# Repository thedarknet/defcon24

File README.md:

# defcon24

Badge Directory has the badge firmware, the eagle files and documentation for components used on the badge.

BadgeGen is a tool used to generate key pairs, and unique radio ids.  This tool can also solve some of the crypto's this was done simply to save typing on the badge itself.

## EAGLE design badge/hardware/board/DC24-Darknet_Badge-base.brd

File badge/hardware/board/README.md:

# Badge hardware

	DC24-Darknet_Badge.*		The starting circuit which has both the base and the shield included
	DC24-Darknet_Badge-base.*	The final base board with puzzles in the silk screen
	DC24-Darknet_Badge-shield.*	The final shield board with puzzles in the silk screen

Note to get the boards made at OSH Park, you need to submit the individual boards base and shield. 
The combined file is strictly for the full schematic.

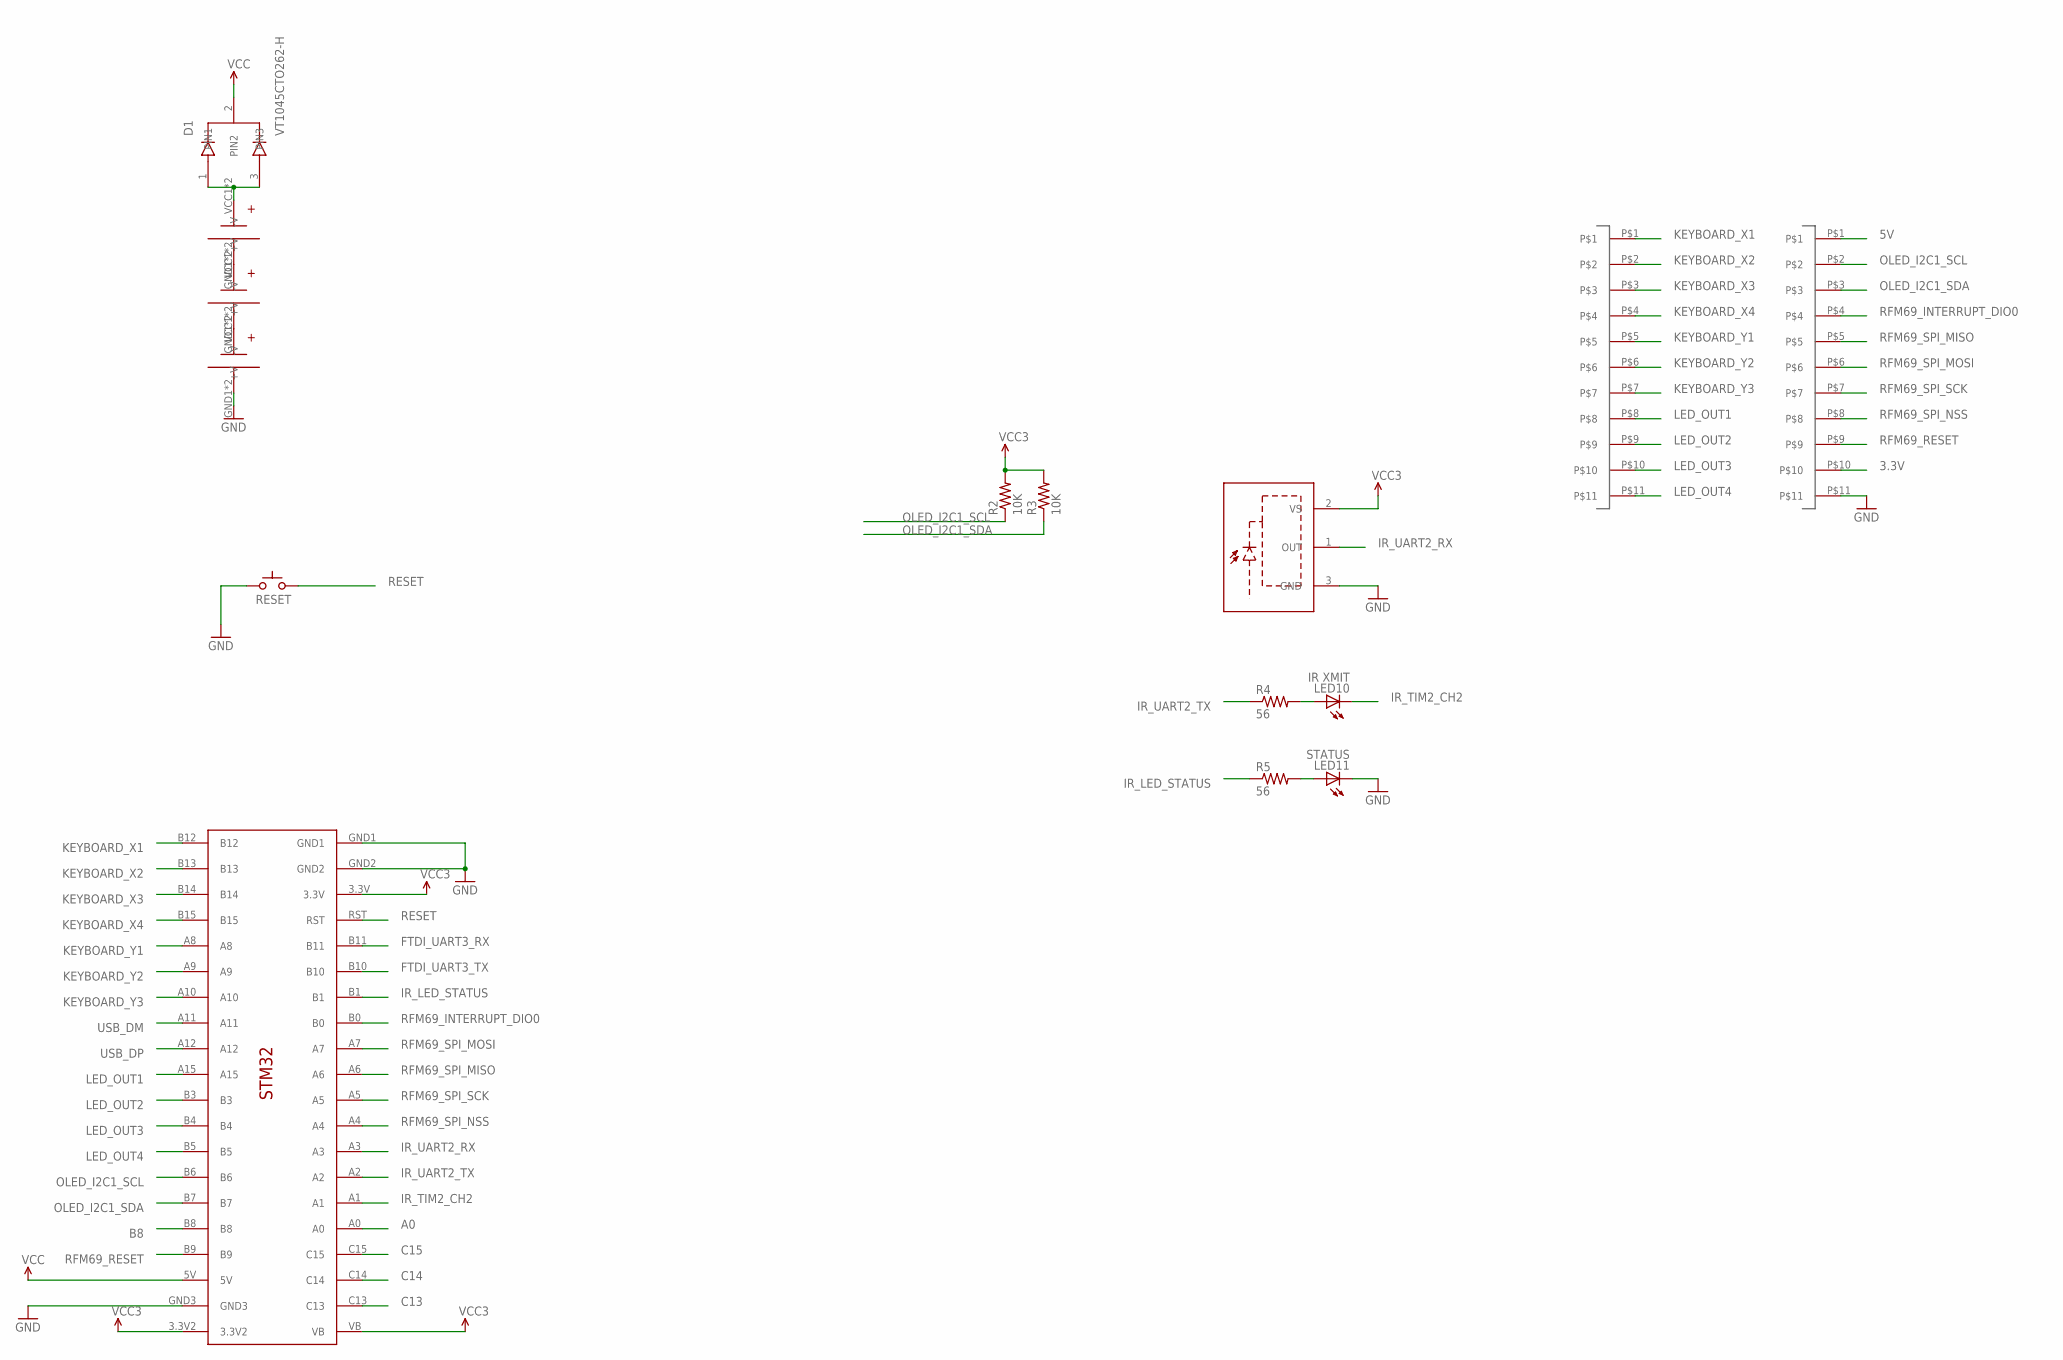
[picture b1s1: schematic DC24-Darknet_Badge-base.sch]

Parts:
D1: VT1045CTO262-H; TO262-H
LED10: IR XMIT; LED5MM-EDGE
LED11: STATUS; LED5MM-EDGE
R2, R3: 10K; AXIAL-0.3
R4, R5: 56; AXIAL-0.3
RESET: SWITCH_TACTILETACTILE-2PIN-NARROW; TACTILE-2PIN-NARROW
U1: SOP22; IR-MODULE
U$3, U$4, U$5: AAA_BATTERYAAA_BATTERY_CLIP; AAA_BATTERY_CLIP
U$14, U$17: HEADER_11PIN; 1X11
U$15: STM32_DEV_BOARDSTM32_DEV_BOARD; STM32_DEV_BOARD

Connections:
3.3V: R2.P$2 (2), R3.P$2 (2), U1.2 (VS), U$15.3.3V, U$15.3.3V2, U$15.VB, U$17.P$10
5V: D1.2 (PIN2), U$15.5V, U$17.P$1
A0: U$15.A0
B8: U$15.B8
C13: U$15.C13
C14: U$15.C14
C15: U$15.C15
FTDI_UART3_RX: U$15.B11
FTDI_UART3_TX: U$15.B10
GND: LED11.K (C), RESET.P$2 (C), U1.3 (GND), U$5.GND1 (-V), U$5.GND2 (-V), U$15.GND1, U$15.GND2, U$15.GND3, U$17.P$11
IR_LED_STATUS: R5.P$1 (1), U$15.B1
IR_TIM2_CH2: LED10.K (C), U$15.A1
IR_UART2_RX: U1.1 (OUT), U$15.A3
IR_UART2_TX: R4.P$1 (1), U$15.A2
KEYBOARD_X1: U$14.P$1, U$15.B12
KEYBOARD_X2: U$14.P$2, U$15.B13
KEYBOARD_X3: U$14.P$3, U$15.B14
KEYBOARD_X4: U$14.P$4, U$15.B15
KEYBOARD_Y1: U$14.P$5, U$15.A8
KEYBOARD_Y2: U$14.P$6, U$15.A9
KEYBOARD_Y3: U$14.P$7, U$15.A10
LED_OUT1: U$14.P$8, U$15.A15
LED_OUT2: U$14.P$9, U$15.B3
LED_OUT3: U$14.P$10, U$15.B4
LED_OUT4: U$14.P$11, U$15.B5
unnamed: LED10.A, R4.P$2 (2)
unnamed: LED11.A, R5.P$2 (2)
unnamed: D1.1 (PIN1), D1.3 (PIN3), U$3.VCC1 (+V), U$3.VCC2 (+V)
unnamed: U$3.GND1 (-V), U$3.GND2 (-V), U$4.VCC1 (+V), U$4.VCC2 (+V)
unnamed: U$4.GND1 (-V), U$4.GND2 (-V), U$5.VCC1 (+V), U$5.VCC2 (+V)
OLED_I2C1_SCL: R2.P$1 (1), U$15.B6, U$17.P$2
OLED_I2C1_SDA: R3.P$1 (1), U$15.B7, U$17.P$3
RESET: RESET.P$1 (A), U$15.RST
RFM69_INTERRUPT_DIO0: U$15.B0, U$17.P$4
RFM69_RESET: U$15.B9, U$17.P$9
RFM69_SPI_MISO: U$15.A6, U$17.P$5
RFM69_SPI_MOSI: U$15.A7, U$17.P$6
RFM69_SPI_NSS: U$15.A4, U$17.P$8
RFM69_SPI_SCK: U$15.A5, U$17.P$7
USB_DM: U$15.A11
USB_DP: U$15.A12

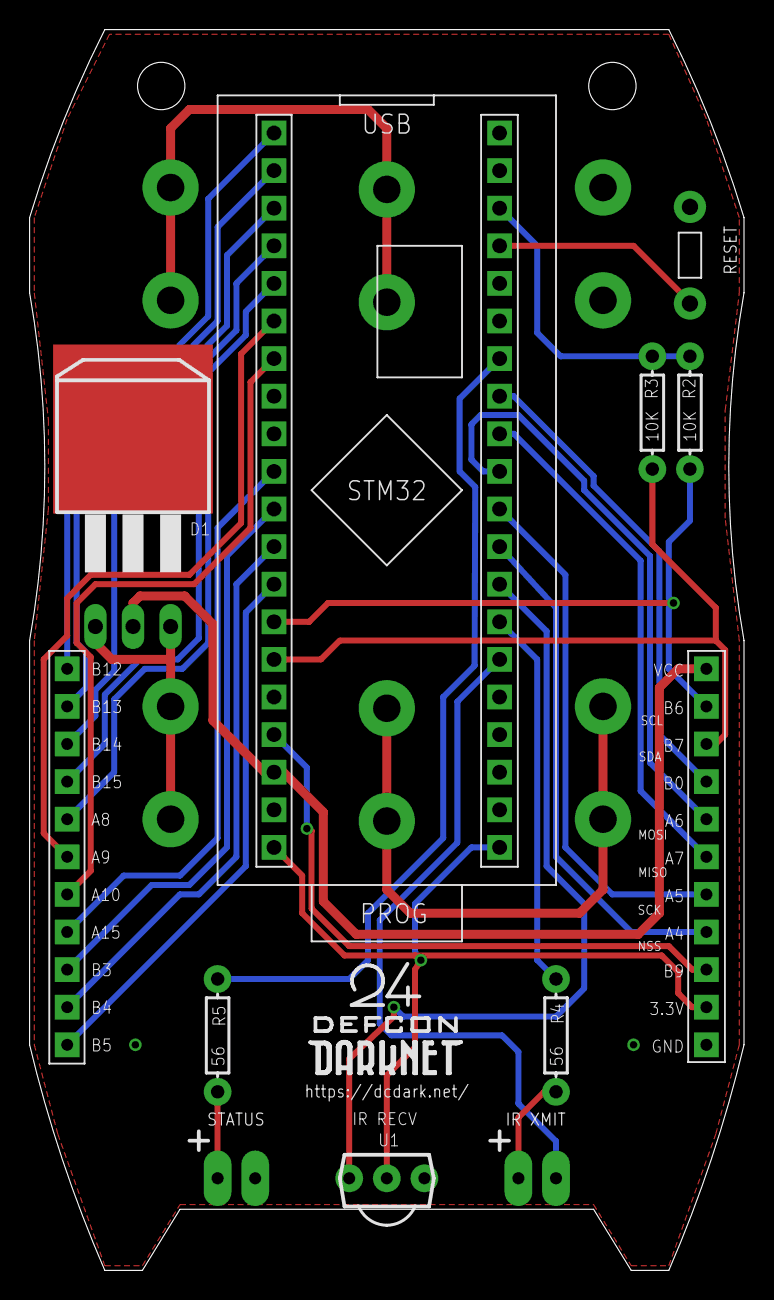
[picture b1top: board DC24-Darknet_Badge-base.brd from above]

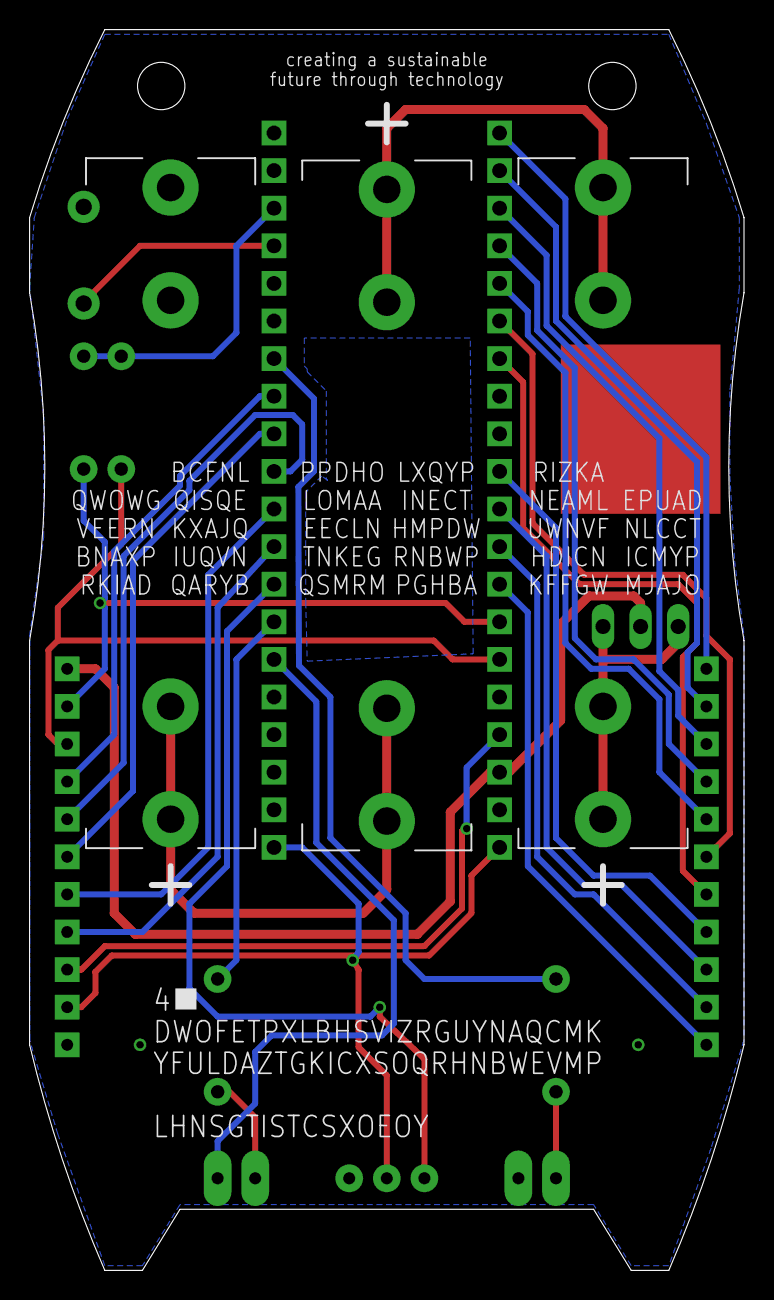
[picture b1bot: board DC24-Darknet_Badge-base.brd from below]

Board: 2 copper layers, 48.3 x 83.8 mm, 15 parts (3 on the bottom side), 32 nets.

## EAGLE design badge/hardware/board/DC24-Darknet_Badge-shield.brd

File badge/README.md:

Install Dev Env:
* go here:  http://gnuarmeclipse.github.io/ for background and step by step

Basic steps:

* Install eclipse Luna CDT (c++ env)

* add a new market place:  

name: GNU ARM Eclipse Plug-ins
URL: http://gnuarmeclipse.sourceforge.net/updates

You will see the ecplise arm plugin select it and it will install for you.

If you get complaints about missing software I found these links helpful.

* apt-get install gcc-arm-none-eabi (or something close to that)

* apt-get install openocd Or download from to configure openocd in eclipse look here: http://gnuarmeclipse.github.io/debug/openocd/ OR to download new version of openocd:  http://gnuarmeclipse.github.io/openocd/download/

Then close this repo and then import this directory into you're workspace (remeber to uncheck the option to copy all files to your workspace).

Debug configuration:

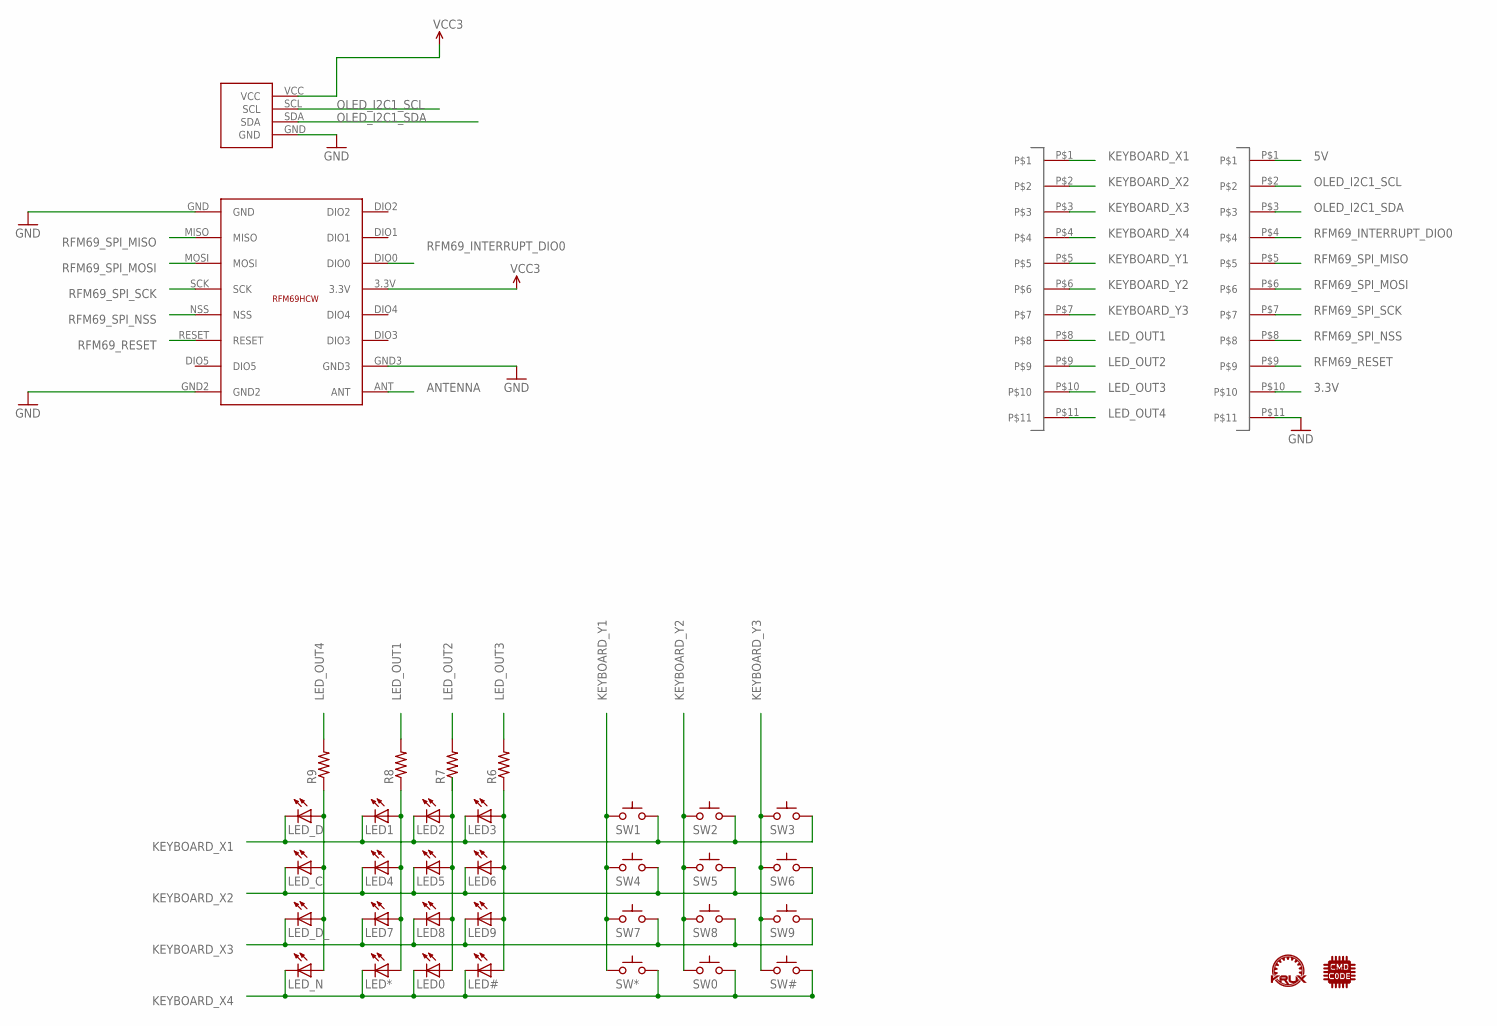
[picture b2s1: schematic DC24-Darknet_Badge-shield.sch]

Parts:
LED0, LED1, LED2, LED3, LED4, LED5, LED6, LED7, LED8, LED9: LEDREVERSEMOUNT; GULLWING_LED
LED#: LEDREVERSEMOUNT; GULLWING_LED
LED*: LEDREVERSEMOUNT; GULLWING_LED
LED_C: LEDREVERSEMOUNT; GULLWING_LED
LED_D: LEDREVERSEMOUNT; GULLWING_LED
LED_D_: LEDREVERSEMOUNT; GULLWING_LED
LED_N: LEDREVERSEMOUNT; GULLWING_LED
R6, R7, R8, R9: RESISTOR1206; 1206
SW0, SW1, SW2, SW3, SW4, SW5, SW6, SW7, SW8, SW9: SWITCH_TACTILETACTILE-2PIN-NARROW; TACTILE-2PIN-NARROW
SW#: SWITCH_TACTILETACTILE-2PIN-NARROW; TACTILE-2PIN-NARROW
SW*: SWITCH_TACTILETACTILE-2PIN-NARROW; TACTILE-2PIN-NARROW
U$1: I2C_0.96_OLEDOLED; I2C_0.96_OLED
U$2: RFM69HCWRFN69HCWSMD; 16PIN-PCB-SMD
U$6, U$13: HEADER_11PIN; 1X11
U$21: KRUX_LOGO
U$23: CMD_C0DE_LOGO

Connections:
3.3V: U$1.VCC, U$2.3.3V, U$13.P$10
5V: U$13.P$1
ANTENNA: U$2.ANT
GND: U$1.GND, U$2.GND, U$2.GND2, U$2.GND3, U$13.P$11
KEYBOARD_X1: LED1.C, LED2.C, LED3.C, LED_D.C, SW1.P$1 (A), SW2.P$1 (A), SW3.P$1 (A), U$6.P$1
KEYBOARD_X2: LED4.C, LED5.C, LED6.C, LED_C.C, SW4.P$1 (A), SW5.P$1 (A), SW6.P$1 (A), U$6.P$2
KEYBOARD_X3: LED7.C, LED8.C, LED9.C, LED_D_.C, SW7.P$1 (A), SW8.P$1 (A), SW9.P$1 (A), U$6.P$3
KEYBOARD_X4: LED0.C, LED#.C, LED*.C, LED_N.C, SW0.P$1 (A), SW#.P$1 (A), SW*.P$1 (A), U$6.P$4
KEYBOARD_Y1: SW1.P$2 (C), SW4.P$2 (C), SW7.P$2 (C), SW*.P$2 (C), U$6.P$5
KEYBOARD_Y2: SW0.P$2 (C), SW2.P$2 (C), SW5.P$2 (C), SW8.P$2 (C), U$6.P$6
KEYBOARD_Y3: SW3.P$2 (C), SW6.P$2 (C), SW9.P$2 (C), SW#.P$2 (C), U$6.P$7
LED_OUT1: R8.2, U$6.P$8
LED_OUT2: R7.2, U$6.P$9
LED_OUT3: R6.2, U$6.P$10
LED_OUT4: R9.2, U$6.P$11
unnamed: LED3.A, LED6.A, LED9.A, LED#.A, R6.1
unnamed: LED0.A, LED2.A, LED5.A, LED8.A, R7.1
unnamed: LED1.A, LED4.A, LED7.A, LED*.A, R8.1
unnamed: LED_C.A, LED_D.A, LED_D_.A, LED_N.A, R9.1
OLED_I2C1_SCL: U$1.SCL, U$13.P$2
OLED_I2C1_SDA: U$1.SDA, U$13.P$3
RFM69_INTERRUPT_DIO0: U$2.DIO0, U$13.P$4
RFM69_RESET: U$2.RESET, U$13.P$9
RFM69_SPI_MISO: U$2.MISO, U$13.P$5
RFM69_SPI_MOSI: U$2.MOSI, U$13.P$6
RFM69_SPI_NSS: U$2.NSS, U$13.P$8
RFM69_SPI_SCK: U$2.SCK, U$13.P$7

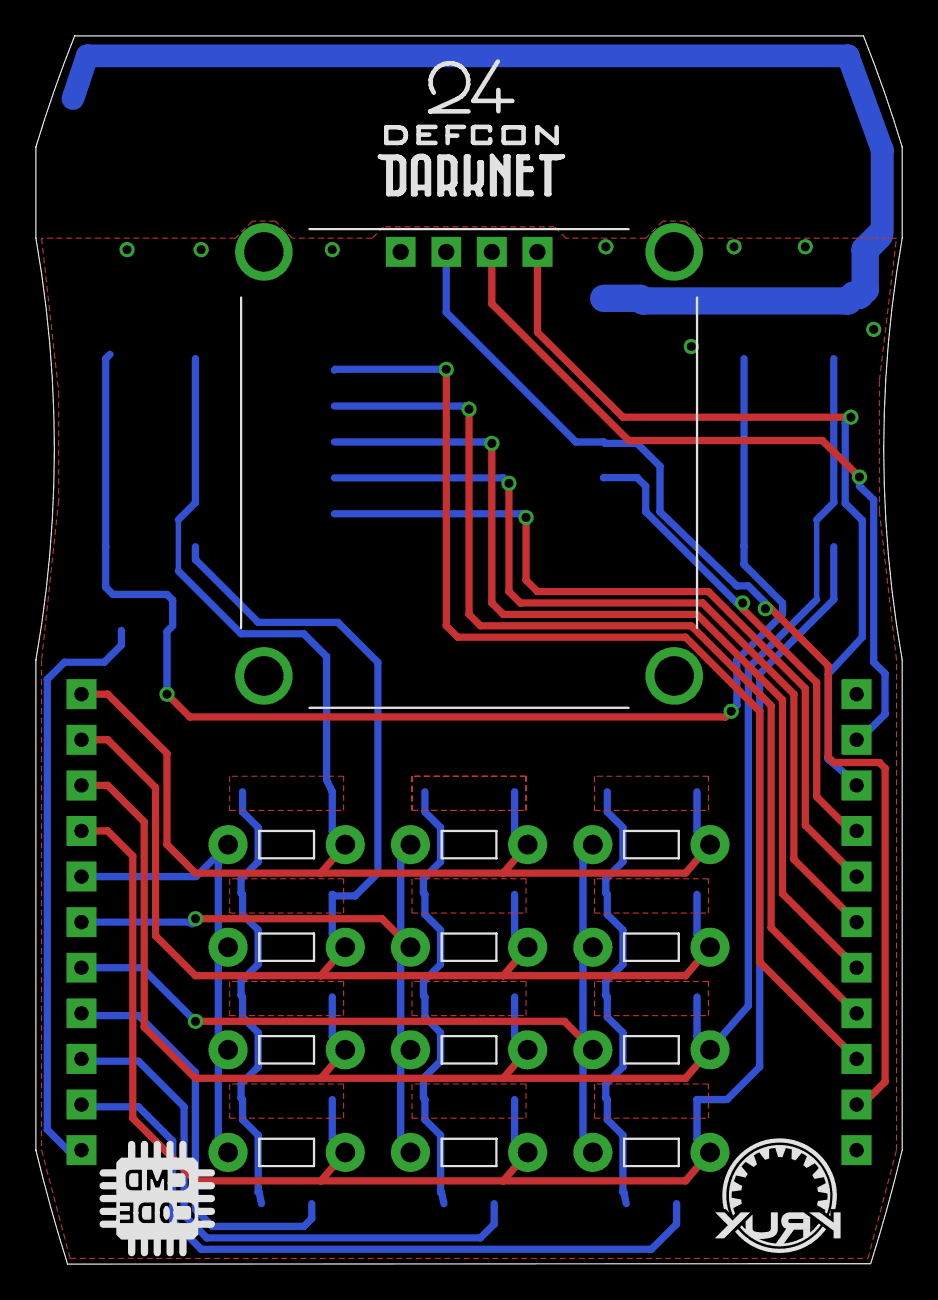
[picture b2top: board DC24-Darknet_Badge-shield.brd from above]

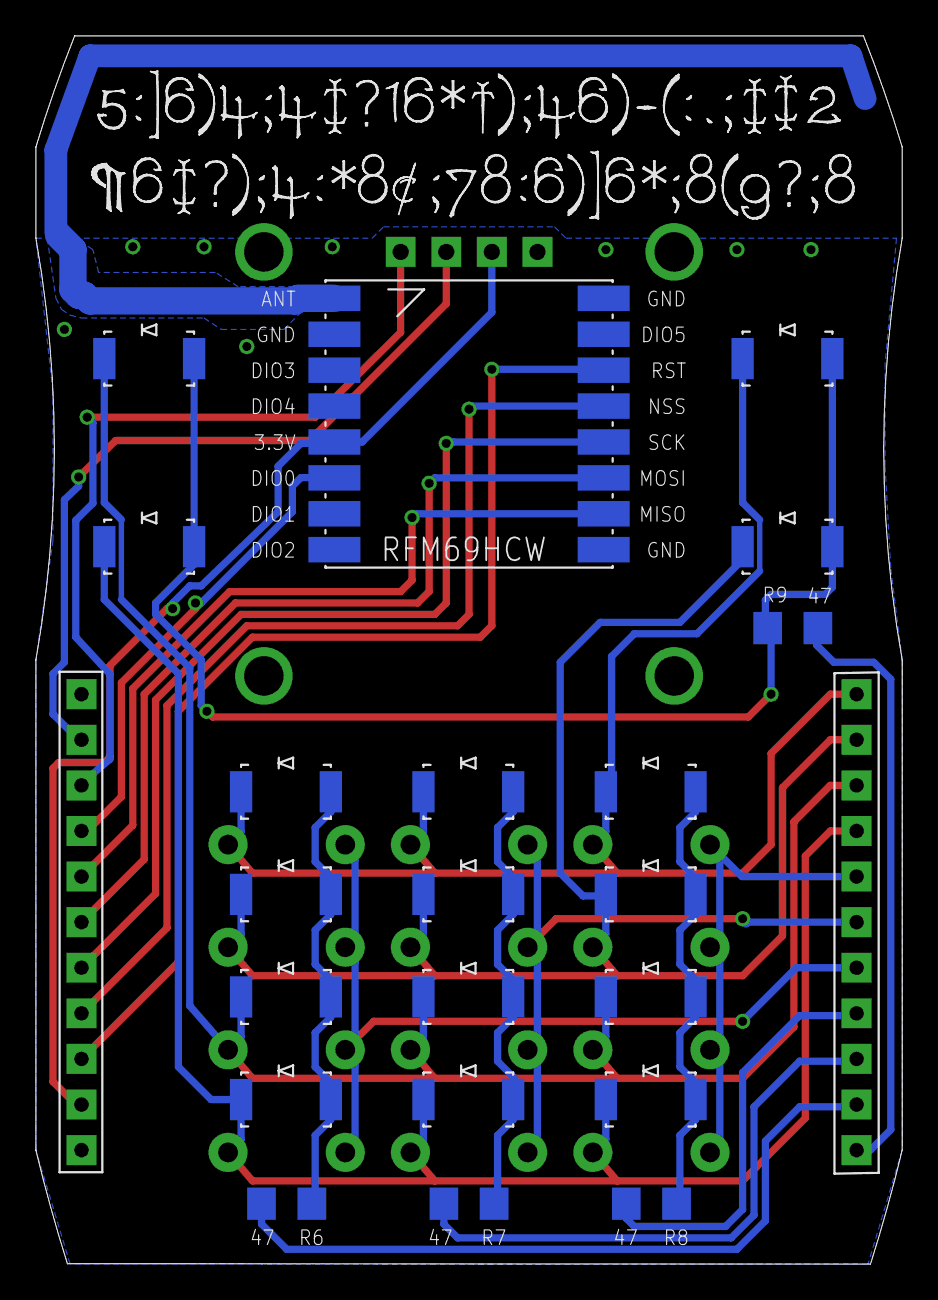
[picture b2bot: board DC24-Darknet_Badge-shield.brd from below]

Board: 2 copper layers, 48.3 x 68.4 mm, 38 parts (23 on the bottom side), 25 nets.

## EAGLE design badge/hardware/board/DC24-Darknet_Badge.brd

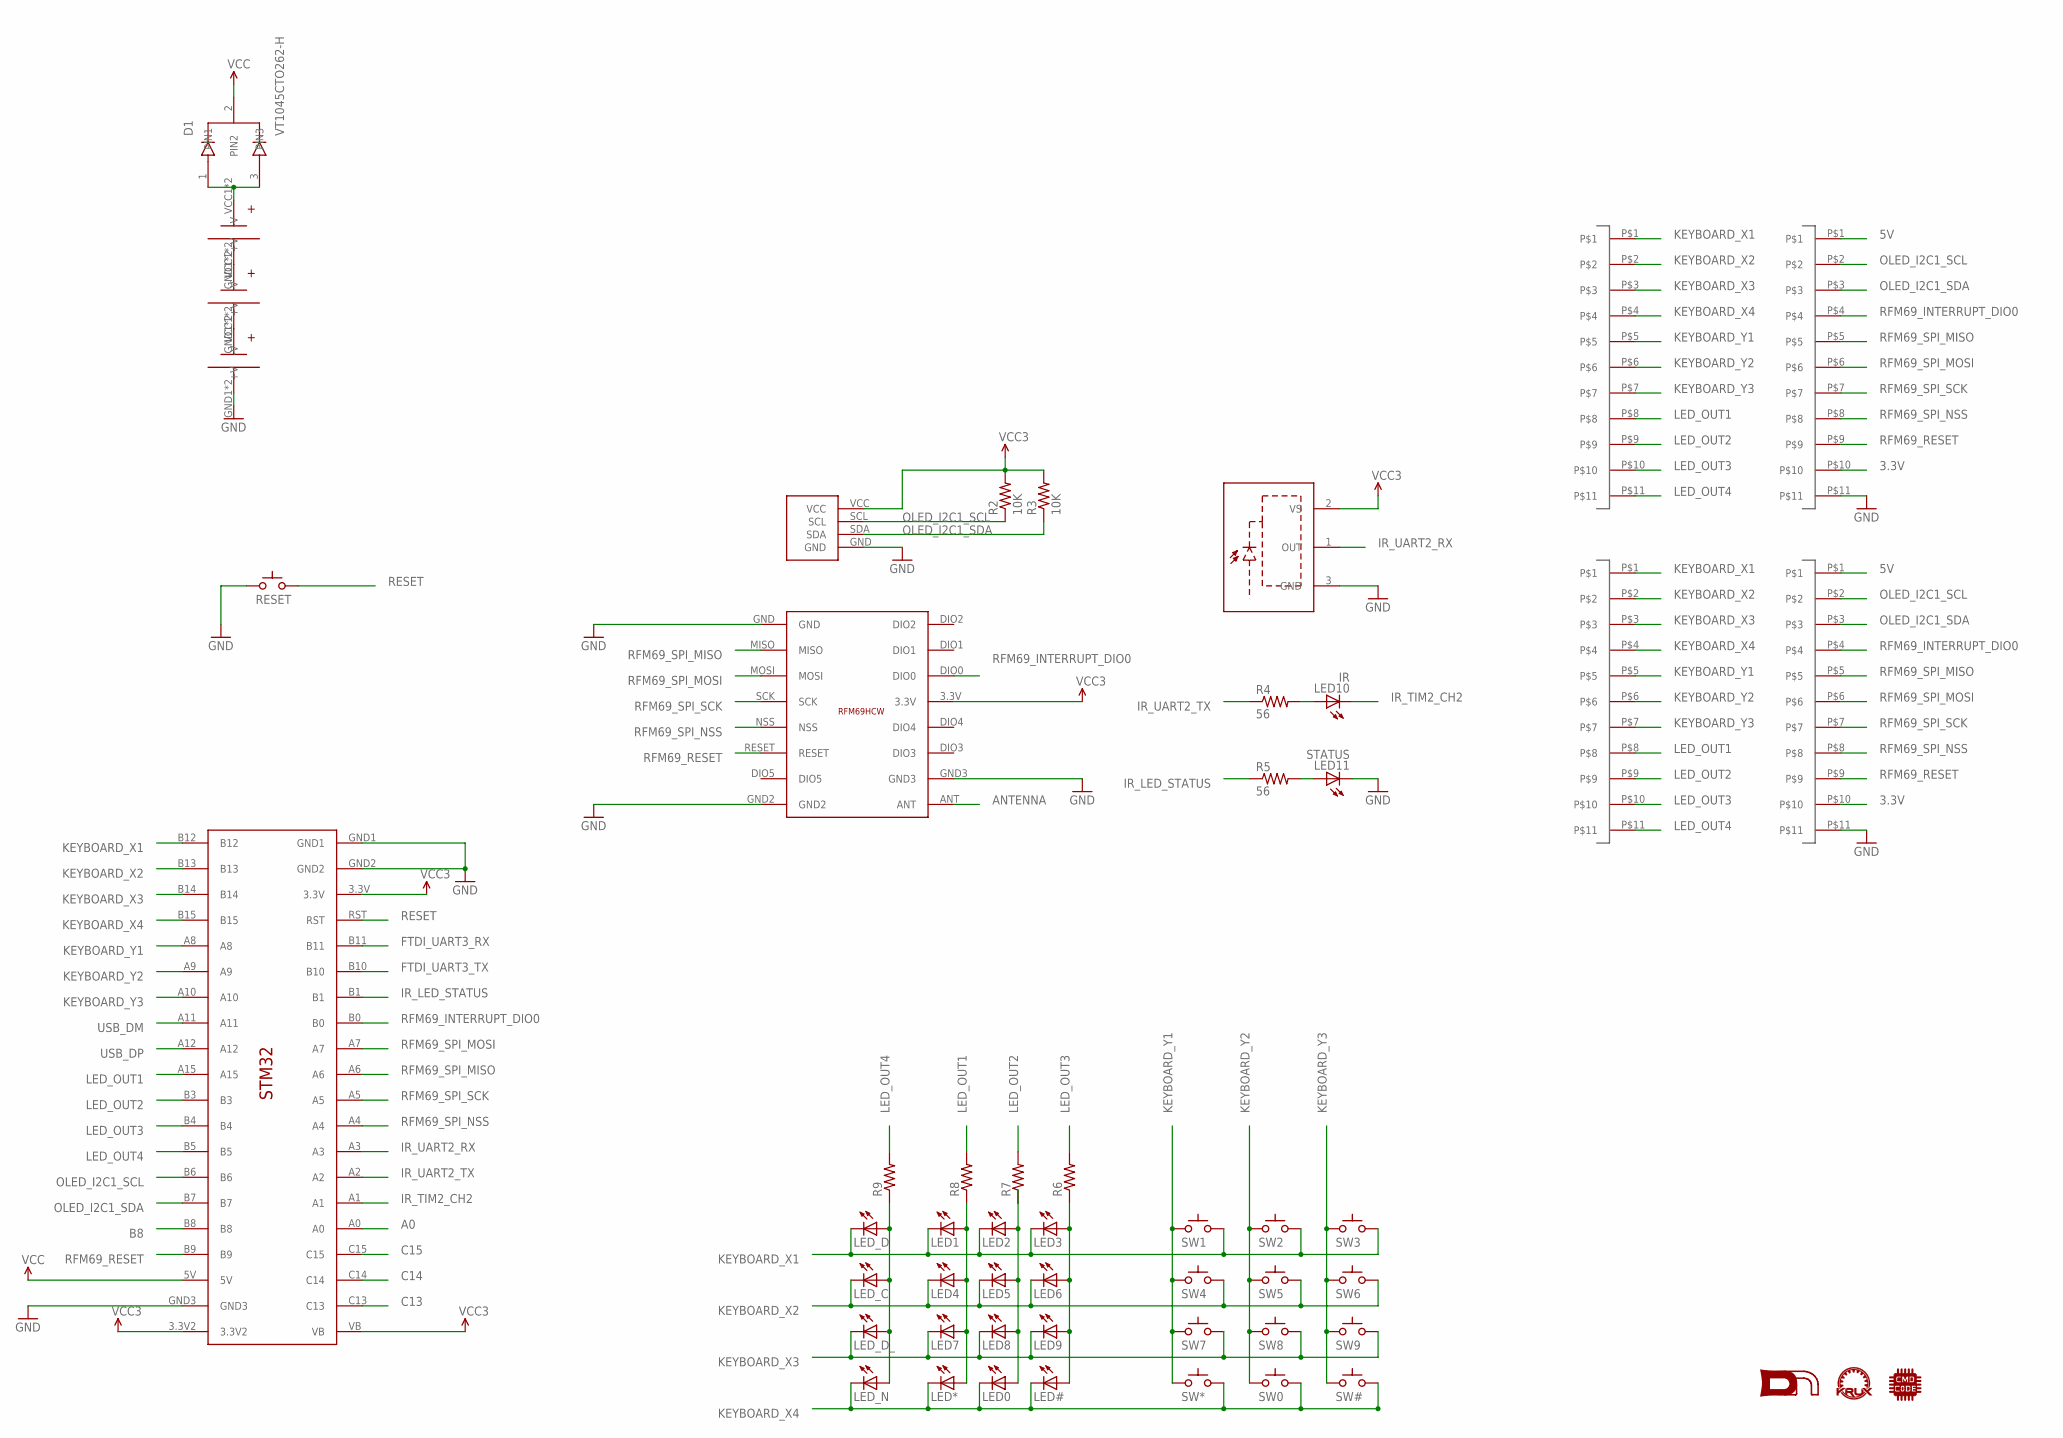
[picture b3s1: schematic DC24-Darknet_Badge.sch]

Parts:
D1: VT1045CTO262-H; TO262-H
LED0, LED1, LED2, LED3, LED4, LED5, LED6, LED7, LED8, LED9: LEDREVERSEMOUNT; GULLWING_LED
LED10: IR; LED5MM-EDGE
LED11: STATUS; LED5MM-EDGE
LED#: LEDREVERSEMOUNT; GULLWING_LED
LED*: LEDREVERSEMOUNT; GULLWING_LED
LED_C: LEDREVERSEMOUNT; GULLWING_LED
LED_D: LEDREVERSEMOUNT; GULLWING_LED
LED_D_: LEDREVERSEMOUNT; GULLWING_LED
LED_N: LEDREVERSEMOUNT; GULLWING_LED
Q1: SOP22; IR-MODULE
R2, R3: 10K; AXIAL-0.3
R4, R5: 56; AXIAL-0.3
R6, R7, R8, R9: RESISTOR1206; 1206
RESET: SWITCH_TACTILETACTILE-2PIN-NARROW; TACTILE-2PIN-NARROW
SW0, SW1, SW2, SW3, SW4, SW5, SW6, SW7, SW8, SW9: SWITCH_TACTILETACTILE-2PIN-NARROW; TACTILE-2PIN-NARROW
SW#: SWITCH_TACTILETACTILE-2PIN-NARROW; TACTILE-2PIN-NARROW
SW*: SWITCH_TACTILETACTILE-2PIN-NARROW; TACTILE-2PIN-NARROW
U$1: I2C_0.96_OLEDOLED; I2C_0.96_OLED
U$2: RFM69HCWRFN69HCWSMD; 16PIN-PCB-SMD
U$3, U$4, U$5: AAA_BATTERYAAA_BATTERY_CLIP; AAA_BATTERY_CLIP
U$6, U$13, U$14, U$17: HEADER_11PIN; 1X11
U$15: STM32_DEV_BOARDSTM32_DEV_BOARD; STM32_DEV_BOARD
U$21: KRUX_LOGO
U$22: DN_LOGO
U$23: CMD_C0DE_LOGO

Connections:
3.3V: Q1.2 (VS), R2.P$2 (2), R3.P$2 (2), U$1.VCC, U$2.3.3V, U$13.P$10, U$15.3.3V, U$15.3.3V2, U$15.VB, U$17.P$10
5V: D1.2 (PIN2), U$13.P$1, U$15.5V, U$17.P$1
A0: U$15.A0
ANTENNA: U$2.ANT
B8: U$15.B8
C13: U$15.C13
C14: U$15.C14
C15: U$15.C15
FTDI_UART3_RX: U$15.B11
FTDI_UART3_TX: U$15.B10
GND: LED11.K (C), Q1.3 (GND), RESET.P$2 (C), U$1.GND, U$2.GND, U$2.GND2, U$2.GND3, U$5.GND1 (-V), U$5.GND2 (-V), U$13.P$11, U$15.GND1, U$15.GND2, U$15.GND3, U$17.P$11
IR_LED_STATUS: R5.P$1 (1), U$15.B1
IR_TIM2_CH2: LED10.K (C), U$15.A1
IR_UART2_RX: Q1.1 (OUT), U$15.A3
IR_UART2_TX: R4.P$1 (1), U$15.A2
KEYBOARD_X1: LED1.C, LED2.C, LED3.C, LED_D.C, SW1.P$1 (A), SW2.P$1 (A), SW3.P$1 (A), U$6.P$1, U$14.P$1, U$15.B12
KEYBOARD_X2: LED4.C, LED5.C, LED6.C, LED_C.C, SW4.P$1 (A), SW5.P$1 (A), SW6.P$1 (A), U$6.P$2, U$14.P$2, U$15.B13
KEYBOARD_X3: LED7.C, LED8.C, LED9.C, LED_D_.C, SW7.P$1 (A), SW8.P$1 (A), SW9.P$1 (A), U$6.P$3, U$14.P$3, U$15.B14
KEYBOARD_X4: LED0.C, LED#.C, LED*.C, LED_N.C, SW0.P$1 (A), SW#.P$1 (A), SW*.P$1 (A), U$6.P$4, U$14.P$4, U$15.B15
KEYBOARD_Y1: SW1.P$2 (C), SW4.P$2 (C), SW7.P$2 (C), SW*.P$2 (C), U$6.P$5, U$14.P$5, U$15.A8
KEYBOARD_Y2: SW0.P$2 (C), SW2.P$2 (C), SW5.P$2 (C), SW8.P$2 (C), U$6.P$6, U$14.P$6, U$15.A9
KEYBOARD_Y3: SW3.P$2 (C), SW6.P$2 (C), SW9.P$2 (C), SW#.P$2 (C), U$6.P$7, U$14.P$7, U$15.A10
LED_OUT1: R8.2, U$6.P$8, U$14.P$8, U$15.A15
LED_OUT2: R7.2, U$6.P$9, U$14.P$9, U$15.B3
LED_OUT3: R6.2, U$6.P$10, U$14.P$10, U$15.B4
LED_OUT4: R9.2, U$6.P$11, U$14.P$11, U$15.B5
unnamed: LED10.A, R4.P$2 (2)
unnamed: LED11.A, R5.P$2 (2)
unnamed: D1.1 (PIN1), D1.3 (PIN3), U$3.VCC1 (+V), U$3.VCC2 (+V)
unnamed: LED3.A, LED6.A, LED9.A, LED#.A, R6.1
unnamed: LED0.A, LED2.A, LED5.A, LED8.A, R7.1
unnamed: LED1.A, LED4.A, LED7.A, LED*.A, R8.1
unnamed: LED_C.A, LED_D.A, LED_D_.A, LED_N.A, R9.1
unnamed: U$3.GND1 (-V), U$3.GND2 (-V), U$4.VCC1 (+V), U$4.VCC2 (+V)
unnamed: U$4.GND1 (-V), U$4.GND2 (-V), U$5.VCC1 (+V), U$5.VCC2 (+V)
OLED_I2C1_SCL: R2.P$1 (1), U$1.SCL, U$13.P$2, U$15.B6, U$17.P$2
OLED_I2C1_SDA: R3.P$1 (1), U$1.SDA, U$13.P$3, U$15.B7, U$17.P$3
RESET: RESET.P$1 (A), U$15.RST
RFM69_INTERRUPT_DIO0: U$2.DIO0, U$13.P$4, U$15.B0, U$17.P$4
RFM69_RESET: U$2.RESET, U$13.P$9, U$15.B9, U$17.P$9
RFM69_SPI_MISO: U$2.MISO, U$13.P$5, U$15.A6, U$17.P$5
RFM69_SPI_MOSI: U$2.MOSI, U$13.P$6, U$15.A7, U$17.P$6
RFM69_SPI_NSS: U$2.NSS, U$13.P$8, U$15.A4, U$17.P$8
RFM69_SPI_SCK: U$2.SCK, U$13.P$7, U$15.A5, U$17.P$7
USB_DM: U$15.A11
USB_DP: U$15.A12

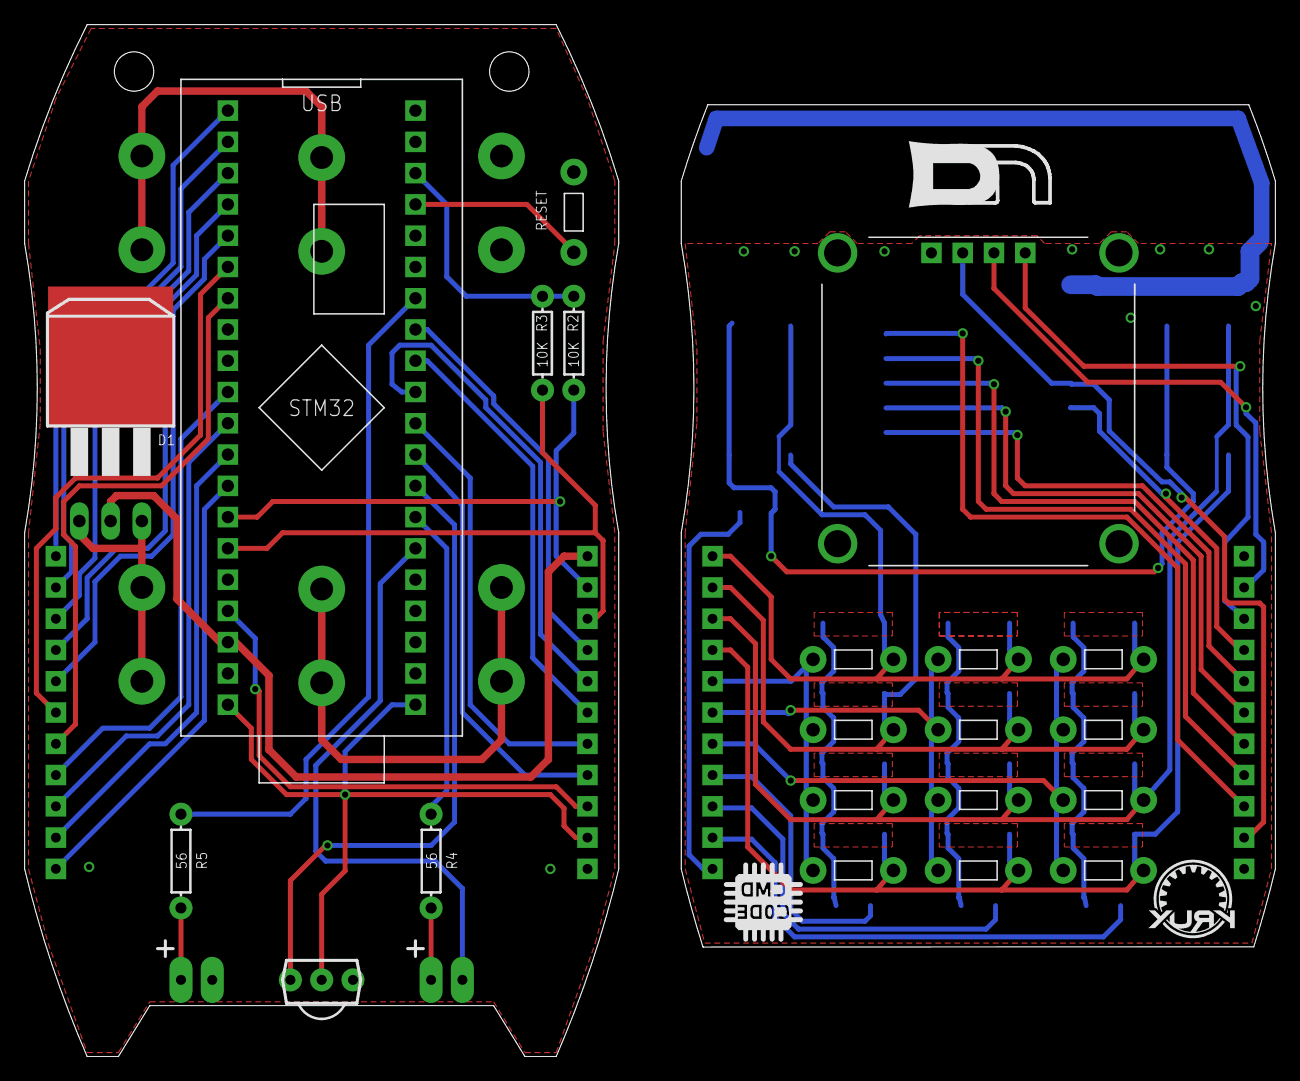
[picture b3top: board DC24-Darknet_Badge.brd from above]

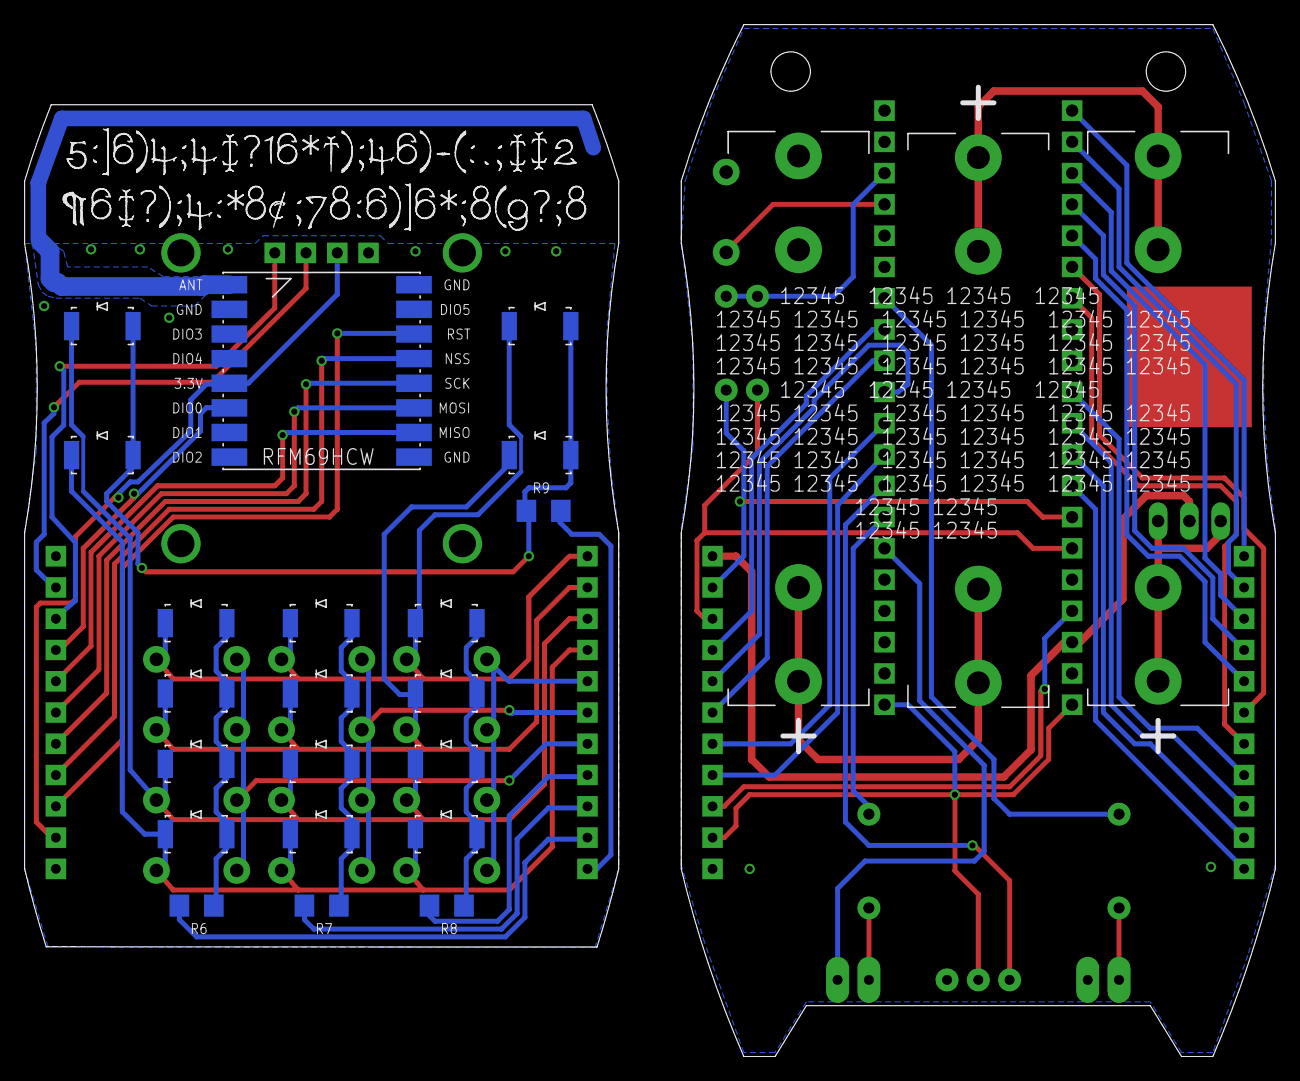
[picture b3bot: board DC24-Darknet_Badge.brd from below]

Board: 2 copper layers, 101.6 x 83.8 mm, 54 parts (26 on the bottom side), 36 nets.

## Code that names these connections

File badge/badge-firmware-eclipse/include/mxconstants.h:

/**
  ******************************************************************************
  * File Name          : mxconstants.h
  * Description        : This file contains the common defines of the application
  ******************************************************************************
  *
  * COPYRIGHT(c) 2016 STMicroelectronics
  *
  * Redistribution and use in source and binary forms, with or without modification,
  * are permitted provided that the following conditions are met:
  *   1. Redistributions of source code must retain the above copyright notice,
  *      this list of conditions and the following disclaimer.
  *   2. Redistributions in binary form must reproduce the above copyright notice,
  *      this list of conditions and the following disclaimer in the documentation
  *      and/or other materials provided with the distribution.
  *   3. Neither the name of STMicroelectronics nor the names of its contributors
  *      may be used to endorse or promote products derived from this software
  *      without specific prior written permission.
  *
  * THIS SOFTWARE IS PROVIDED BY THE COPYRIGHT HOLDERS AND CONTRIBUTORS "AS IS"
  * AND ANY EXPRESS OR IMPLIED WARRANTIES, INCLUDING, BUT NOT LIMITED TO, THE
  * IMPLIED WARRANTIES OF MERCHANTABILITY AND FITNESS FOR A PARTICULAR PURPOSE ARE
  * DISCLAIMED. IN NO EVENT SHALL THE COPYRIGHT HOLDER OR CONTRIBUTORS BE LIABLE
  * FOR ANY DIRECT, INDIRECT, INCIDENTAL, SPECIAL, EXEMPLARY, OR CONSEQUENTIAL
  * DAMAGES (INCLUDING, BUT NOT LIMITED TO, PROCUREMENT OF SUBSTITUTE GOODS OR
  * SERVICES; LOSS OF USE, DATA, OR PROFITS; OR BUSINESS INTERRUPTION) HOWEVER
  * CAUSED AND ON ANY THEORY OF LIABILITY, WHETHER IN CONTRACT, STRICT LIABILITY,
  * OR TORT (INCLUDING NEGLIGENCE OR OTHERWISE) ARISING IN ANY WAY OUT OF THE USE
  * OF THIS SOFTWARE, EVEN IF ADVISED OF THE POSSIBILITY OF SUCH DAMAGE.
  *
  ******************************************************************************
  */
/* Includes ------------------------------------------------------------------*/

/* USER CODE BEGIN Includes */

/* USER CODE END Includes */

/* Private define ------------------------------------------------------------*/

#define IR_TIM2_CH2_Pin GPIO_PIN_1
#define IR_TIM2_CH2_GPIO_Port GPIOA
#define IR_UART2_TX_Pin GPIO_PIN_2
#define IR_UART2_TX_GPIO_Port GPIOA
#define IR_UART2_RX_Pin GPIO_PIN_3
#define IR_UART2_RX_GPIO_Port GPIOA
#define RFM69_SPI_NSS_Pin GPIO_PIN_4
#define RFM69_SPI_NSS_GPIO_Port GPIOA
#define RFM69_SPI1_SCK_Pin GPIO_PIN_5
#define RFM69_SPI1_SCK_GPIO_Port GPIOA
#define RFM69_SPI_MISO_Pin GPIO_PIN_6
#define RFM69_SPI_MISO_GPIO_Port GPIOA
#define RFM69_SPI_MOSI_Pin GPIO_PIN_7
#define RFM69_SPI_MOSI_GPIO_Port GPIOA
#define RFM69_Interrupt_DIO0_Pin GPIO_PIN_0
#define RFM69_Interrupt_DIO0_GPIO_Port GPIOB
#define LED_IR_STATUS_Pin GPIO_PIN_1
#define LED_IR_STATUS_GPIO_Port GPIOB
#define FTDI_USART3_TX_Pin GPIO_PIN_10
#define FTDI_USART3_TX_GPIO_Port GPIOB
#define FTDI_UXART3_RX_Pin GPIO_PIN_11
#define FTDI_UXART3_RX_GPIO_Port GPIOB
#define KEYBOARD_X1_Pin GPIO_PIN_12
#define KEYBOARD_X1_GPIO_Port GPIOB
#define KEYBOARD_X2_Pin GPIO_PIN_13
#define KEYBOARD_X2_GPIO_Port GPIOB
#define KEYBOARD_X3_Pin GPIO_PIN_14
#define KEYBOARD_X3_GPIO_Port GPIOB
#define KEYBOARD_X4_Pin GPIO_PIN_15
#define KEYBOARD_X4_GPIO_Port GPIOB
#define KEYBOARD_Y1_Pin GPIO_PIN_8
#define KEYBOARD_Y1_GPIO_Port GPIOA
#define KEYBOARD_Y2_Pin GPIO_PIN_9
#define KEYBOARD_Y2_GPIO_Port GPIOA
#define KEYBOARD_Y3_Pin GPIO_PIN_10
#define KEYBOARD_Y3_GPIO_Port GPIOA
#define LED_OUT1_Pin GPIO_PIN_15
#define LED_OUT1_GPIO_Port GPIOA
#define LED_OUT2_Pin GPIO_PIN_3
#define LED_OUT2_GPIO_Port GPIOB
#define LED_OUT3_Pin GPIO_PIN_4
#define LED_OUT3_GPIO_Port GPIOB
#define LED_OUT4_Pin GPIO_PIN_5
#define LED_OUT4_GPIO_Port GPIOB
#define OLED_I2C1_SCL_Pin GPIO_PIN_6
#define OLED_I2C1_SCL_GPIO_Port GPIOB
#define OLED_I2C1_SDA_Pin GPIO_PIN_7
#define OLED_I2C1_SDA_GPIO_Port GPIOB
/* USER CODE BEGIN Private defines */

/* USER CODE END Private defines */

/**
  * @}
  */ 

/**
  * @}
*/ 

/************************ (C) COPYRIGHT STMicroelectronics *****END OF FILE****/
